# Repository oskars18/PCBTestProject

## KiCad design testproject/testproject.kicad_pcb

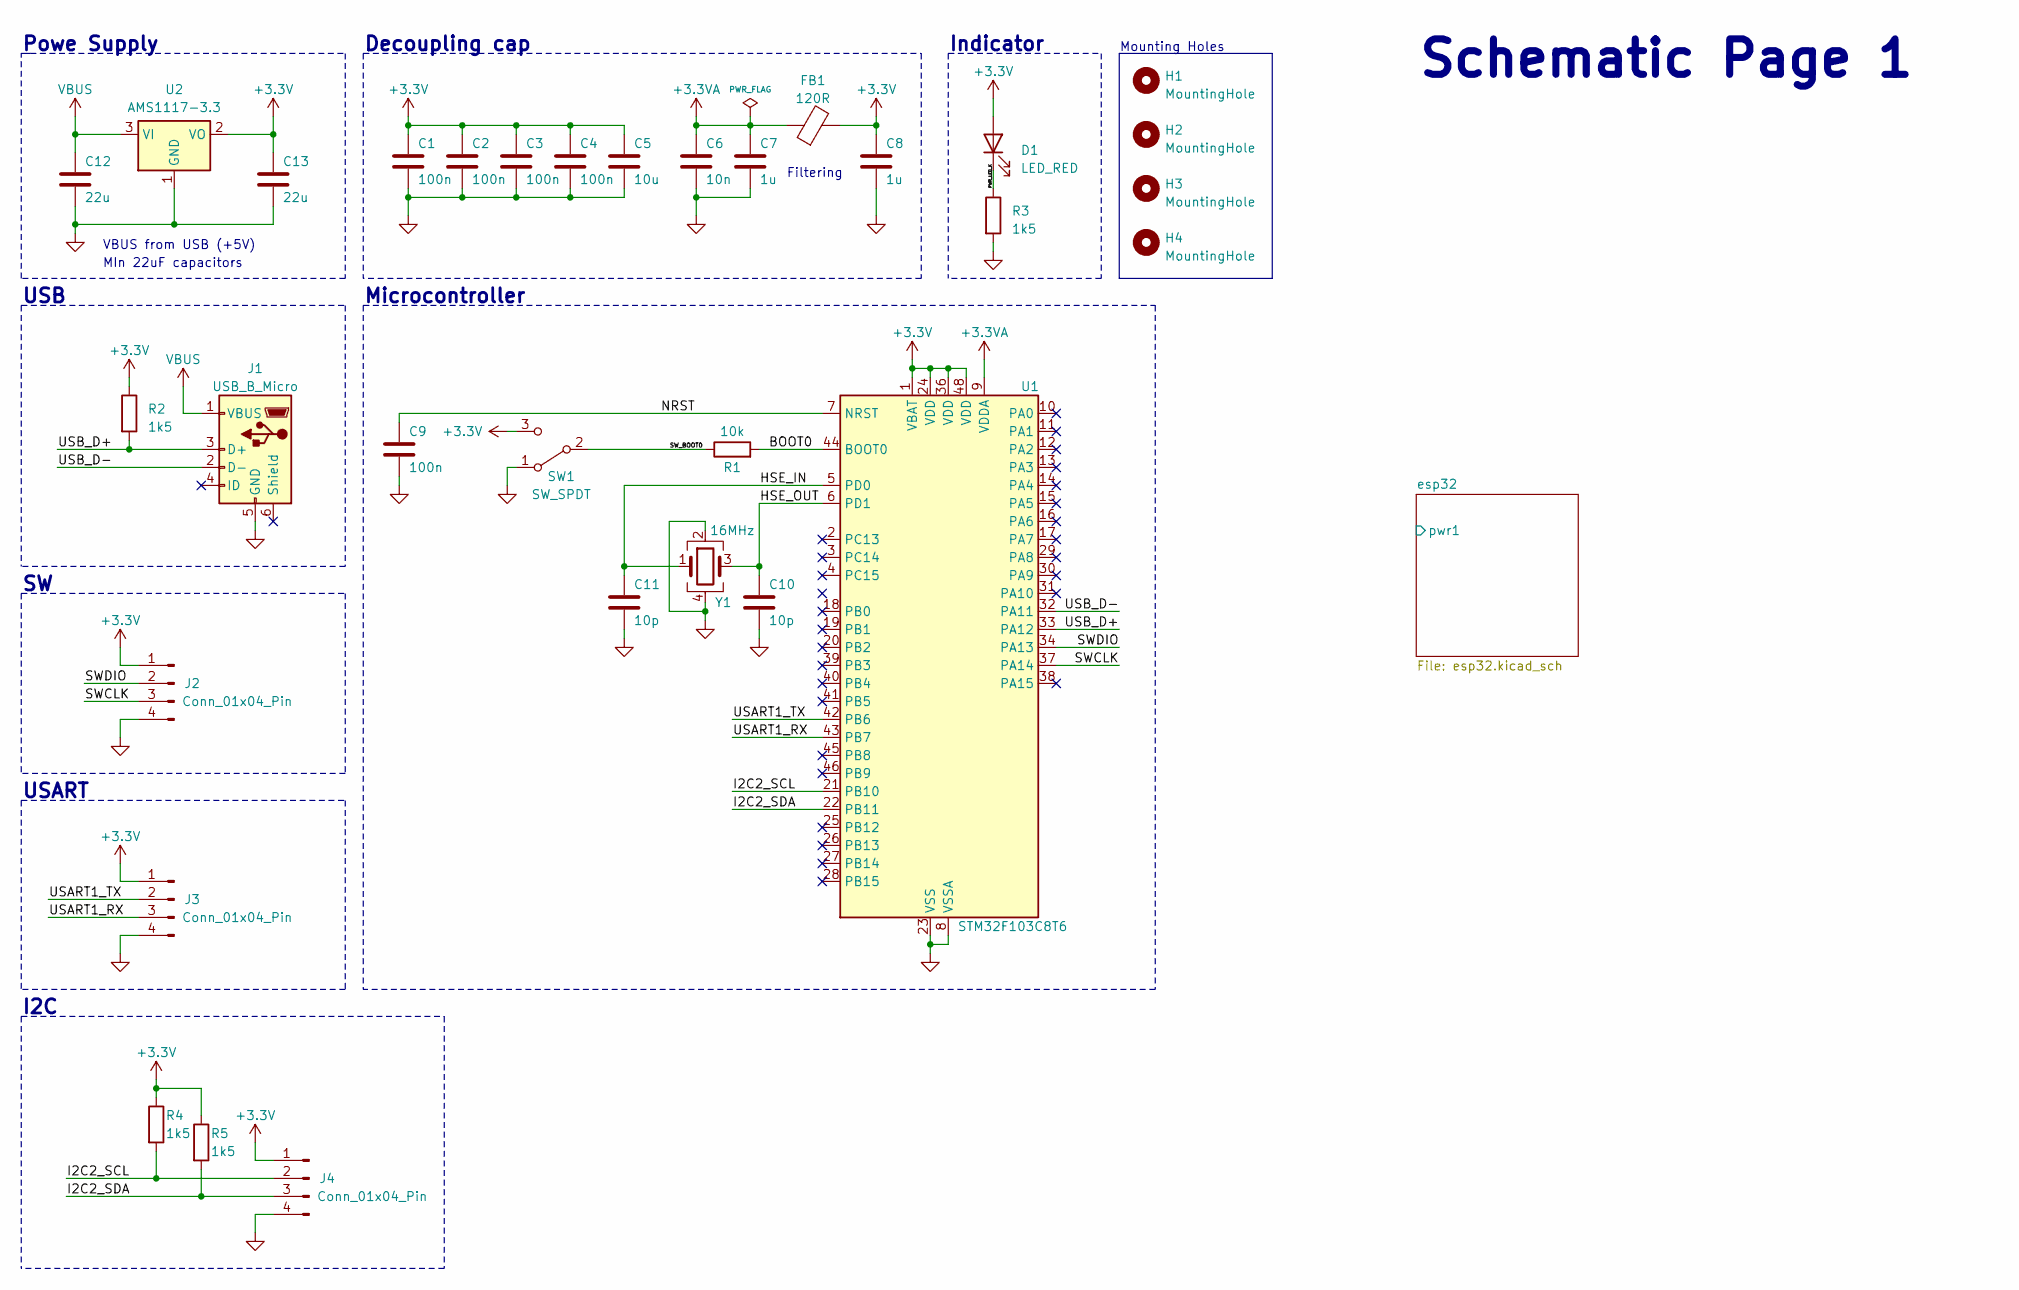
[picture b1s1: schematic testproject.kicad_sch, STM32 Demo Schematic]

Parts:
C1, C2, C3, C4, C9: 100n; C_0402_1005Metric
C5: 10u; C_0603_1608Metric
C6: 10n; C_0603_1608Metric
C7, C8: 1u; C_0402_1005Metric
C10, C11: 10p; C_0402_1005Metric
C12, C13: 22u; C_0805_2012Metric
D1: LED_RED; LED_0603_1608Metric
FB1: 120R; L_0603_1608Metric
H1, H2, H3, H4: MountingHole; MountingHole_2.2mm_M2
J1: USB_B_Micro; USB_Micro-B_Wuerth_629105150521
J2, J3, J4: Conn_01x04_Pin; PinHeader_1x04_P2.54mm_Vertical
R1: 10k; R_0402_1005Metric
R2, R3, R4, R5: 1k5; R_0402_1005Metric
SW1: SW_SPDT; SW_SPDT_PCM12
U1: STM32F103C8T6; LQFP-48_7x7mm_P0.5mm
U2: AMS1117-3.3; SOT-223-3_TabPin2
Y1: 16MHz; Crystal_SMD_3225-4Pin_3.2x2.5mm

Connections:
+3.3V: C1.1, C2.1, C3.1, C4.1, C5.1, C8.1, C13.1, D1.2 (A), FB1.2, J2.1, J3.1, J4.1, R2.1, R4.1, R5.1, SW1.3 (C), U1.1 (VBAT), U1.24 (VDD), U1.36 (VDD), U1.48 (VDD), U2.2 (VO)
+3.3VA: C6.1, C7.1, FB1.1, U1.9 (VDDA)
/BOOT0: R1.2, U1.44 (BOOT0)
/HSE_IN: C11.1, U1.5 (PD0), Y1.1
/HSE_OUT: C10.1, U1.6 (PD1), Y1.3
/I2C2_SCL: J4.2, R4.2, U1.21 (PB10)
/I2C2_SDA: J4.3, R5.2, U1.22 (PB11)
/NRST: C9.1, U1.7 (NRST)
/PWR_LED_K: D1.1 (K), R3.1
/SWCLK: J2.3, U1.37 (PA14)
/SWDIO: J2.2, U1.34 (PA13)
/SW_BOOT0: R1.1, SW1.2 (B)
/USART1_RX: J3.3, U1.43 (PB7)
/USART1_TX: J3.2, U1.42 (PB6)
/USB_D+: J1.3 (D+), R2.2, U1.33 (PA12)
/USB_D-: J1.2 (D-), U1.32 (PA11)
GND: C1.2, C2.2, C3.2, C4.2, C5.2, C6.2, C7.2, C8.2, C9.2, C10.2, C11.2, C12.2, C13.2, J1.5 (GND), J2.4, J3.4, J4.4, R3.2, SW1.1 (A), U1.8 (VSSA), U1.23 (VSS), U1.35 (VSS), U1.47 (VSS), U2.1 (GND), Y1.2, Y1.4
VBUS: C12.1, J1.1 (VBUS), U2.3 (VI)

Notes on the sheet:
I2C
Schematic Page 1
Decoupling cap
VBUS from USB (+5V)
USART
Microcontroller
Indicator
Powe Supply
Mounting Holes
MIn 22uF capacitors
USB
Filtering

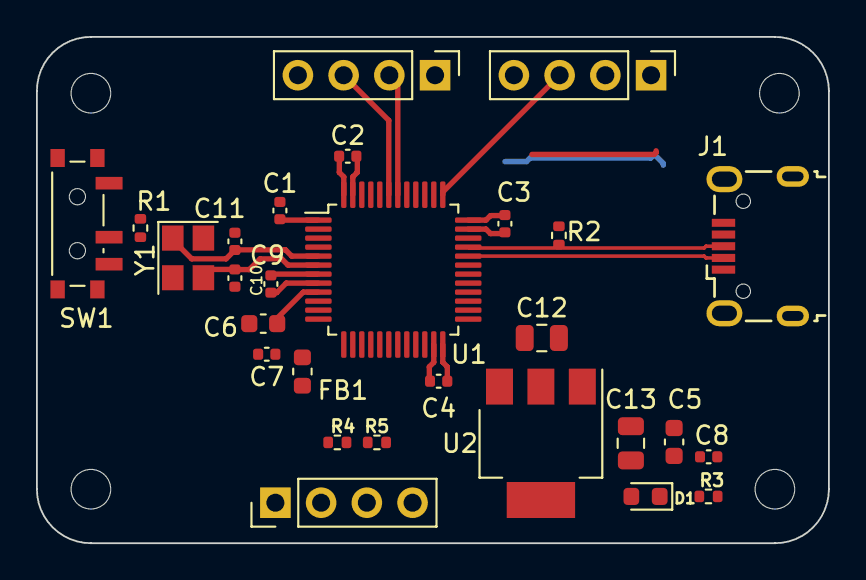
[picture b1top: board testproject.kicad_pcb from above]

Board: 2 copper layers, 44.0 x 28.1 mm, 32 parts (0 on the bottom side), 18 nets.
